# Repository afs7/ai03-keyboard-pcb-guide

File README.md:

# ai03-keyboard-pcb-guide
 keyboard pcb guide and practice

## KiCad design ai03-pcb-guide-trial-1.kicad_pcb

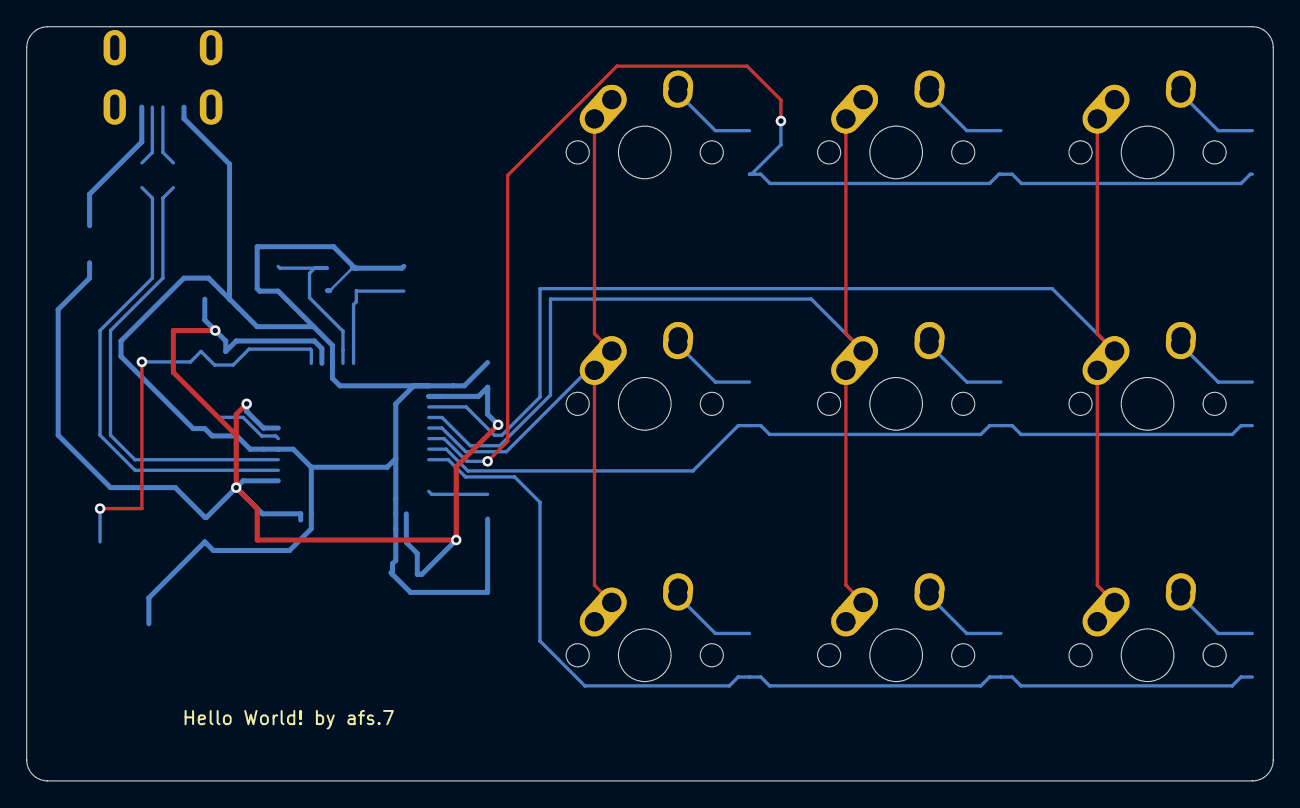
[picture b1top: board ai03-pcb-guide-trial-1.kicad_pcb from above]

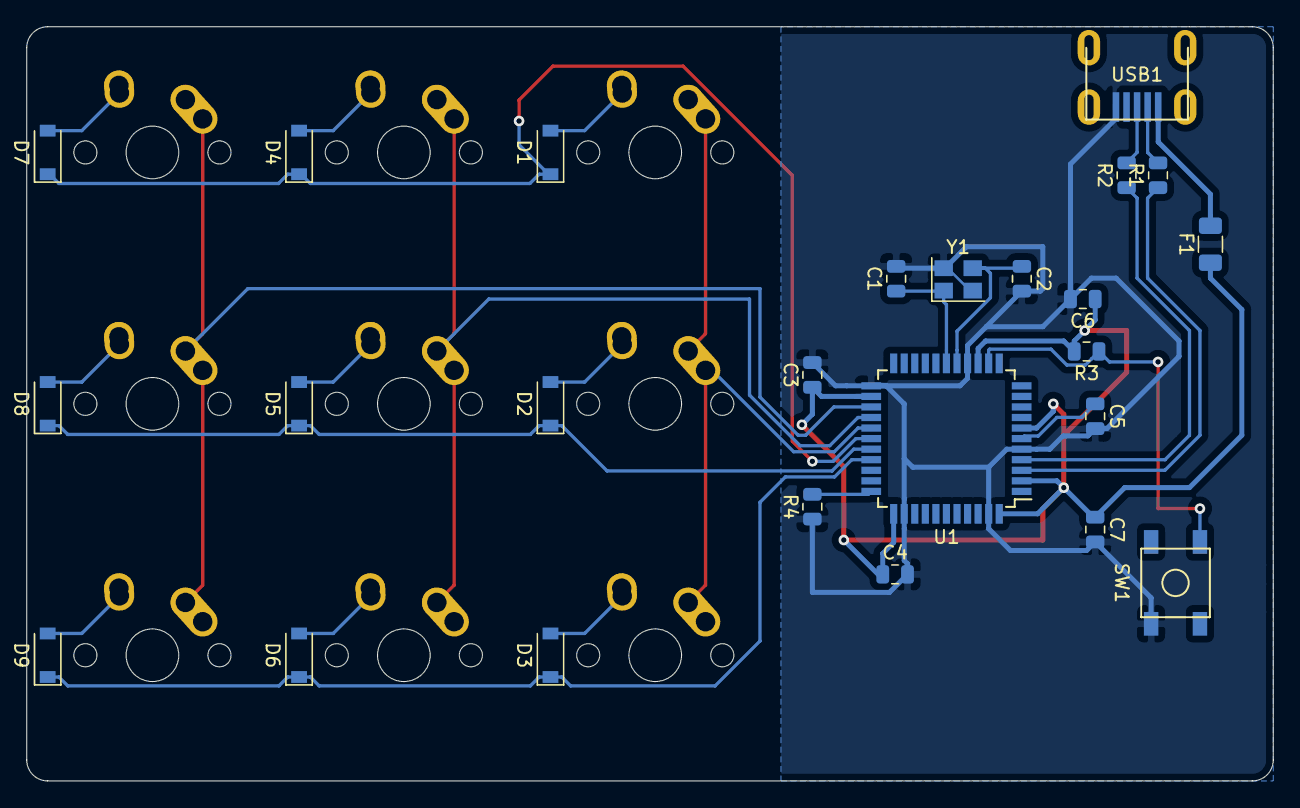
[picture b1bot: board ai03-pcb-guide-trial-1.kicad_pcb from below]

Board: 2 copper layers, 94.5 x 57.2 mm, 34 parts (25 on the bottom side), 27 nets.

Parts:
C1, C2: 22pF; C_0805_2012Metric
C3, C4, C6: 0.1uF; C_0805_2012Metric
C5: 1uF; C_0805_2012Metric
C7: 10uF; C_0805_2012Metric
D1, D2, D3, D4, D5, D6, D7, D8, D9: D_Small; D_SOD-123
F1: 500mA; Fuse_1206_3216Metric
MX1, MX2, MX3, MX4, MX5, MX6, MX7, MX8, MX9: MX-NoLED; MX-1U-NoLED
R1, R2: 22; R_0805_2012Metric
R3, R4: 10k; R_0805_2012Metric
SW1: SW_Push; SKQG-1155865
U1: ATmega32U4-AU; TQFP-44_10x10mm_P0.8mm
USB1: Molex-0548190589
Y1: Crystal_GND24_Small; Crystal_SMD_3225-4Pin_3.2x2.5mm

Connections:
+5V: C3.1, C4.1, C6.1, C7.1, F1.1, R3.2, U1.2, U1.7, U1.14, U1.24, U1.34, U1.44
COL0: MX1.1, MX2.1, MX3.1, U1.27
COL1: MX4.1, MX5.1, MX6.1, U1.26
COL2: MX7.1, MX8.1, MX9.1, U1.25
D+: R2.2, USB1.3
D-: R1.2, USB1.4
GND: C1.2, C2.2, C3.2, C4.2, C5.2, C6.2, C7.2, R4.1, SW1.1, U1.5, U1.15, U1.23, U1.35, U1.43, USB1.1, Y1.2, Y1.4
unnamed: C1.1, U1.17, Y1.1
unnamed: C2.1, U1.16, Y1.3
unnamed: C5.1, U1.6
unnamed: D1.2, MX1.2
unnamed: D2.2, MX2.2
unnamed: D3.2, MX3.2
unnamed: D4.2, MX4.2
unnamed: D5.2, MX5.2
unnamed: D6.2, MX6.2
unnamed: D7.2, MX7.2
unnamed: D8.2, MX8.2
unnamed: D9.2, MX9.2
unnamed: R1.1, U1.3
unnamed: R2.1, U1.4
unnamed: R3.1, SW1.2, U1.13
unnamed: R4.2, U1.33
ROW0: D1.1, D4.1, D7.1, U1.28
ROW1: D2.1, D5.1, D8.1, U1.29
ROW2: D3.1, D6.1, D9.1, U1.30
VCC: F1.2, USB1.5

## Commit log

2021-03-27 Initializing project
2021-03-27 Add submodules
2021-03-27 Add submodules2
2021-03-27 Add footprint libraries
2021-03-27 schematic and footprint bindings
2021-03-27 PCB traced
2021-03-27 Done designing (exporting next)
